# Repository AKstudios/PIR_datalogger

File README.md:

# PIR data logger
A motion/activity data logger that stores time-stamped data on a microSD card whenever there is motion within 3-5m. Approximate battery life: 1-2 years depending on LiPo battery used.

<p align="center">
  
  <br></br>
  
</p>

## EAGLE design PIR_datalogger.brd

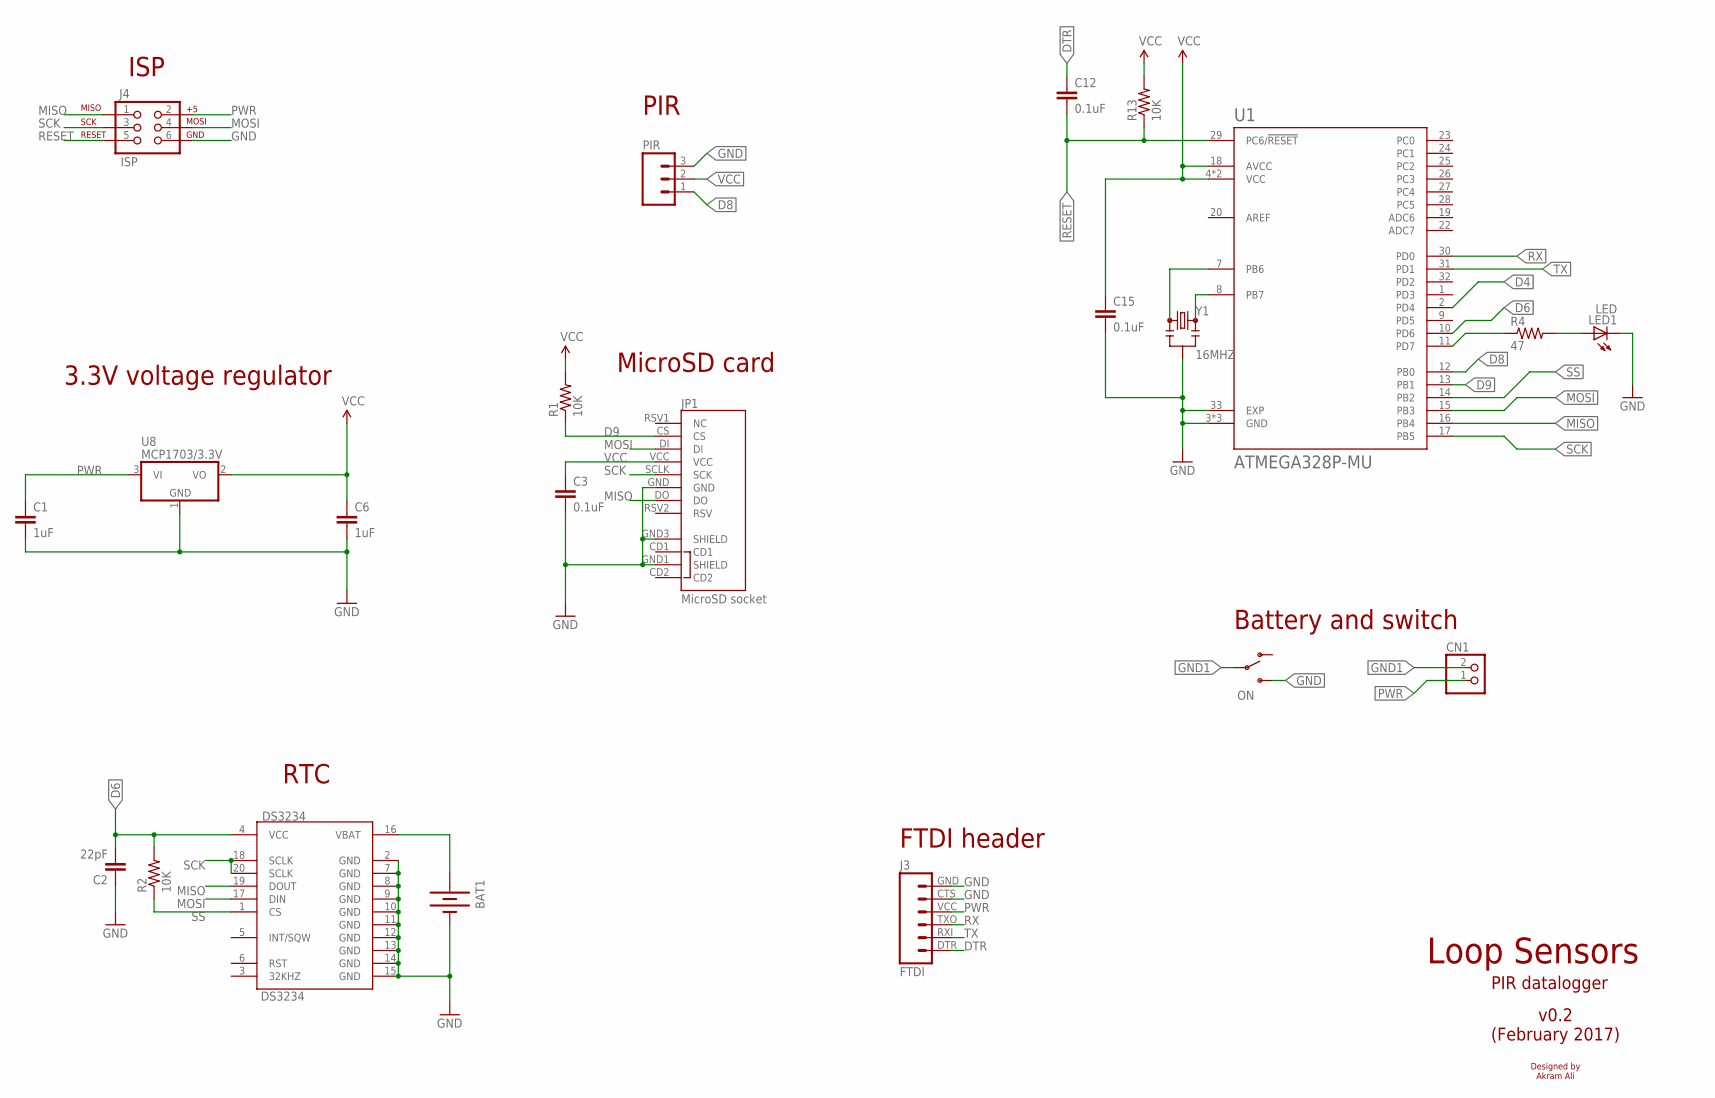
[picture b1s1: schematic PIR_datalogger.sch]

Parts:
BAT1: BATTERY12MM; BATTCON_12MM; MPN 3000
C1, C6: 1uF; 0805; MPN CC0805KKX7R7BB105
C2: 22pF; 0805; MPN AC0805KRX7R9BB104
C3, C12, C15: 0.1uF; 0805; MPN AC0805KRX7R9BB104
CN1: JST_2PIN-SMT-RA; JST-PH-2-SMT-RA
DS3234: DS3234; MPN DS3234S#
J3: FTDI; FTDI_BASIC
J4: ISP; 2X3
JP1: MicroSD socket; MICRO-SD-SOCKET-PP
LED1: LED; CHIPLED_0805; MPN 150080BS75000
ON: SWITCH-SPDT-SMD-A; SWITCH-SPST-SMD-A
PIR: M03PTH; 1X03
R1, R2, R13: 10K; 0805; MPN RC0805JR-0710KL
R4: 47; 0805; MPN RC0805JR-0747RL
U1: ATMEGA328P-MU; QFN50P500X500X100-33N
U8: MCP1703/3.3V; SOT23; MPN MCP1703T-2502E/CB
Y1: 16MHZ; RESONATOR-SMD; MPN CSTCE16M0V53-R0

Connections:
D4: U1.2 (PD4)
D6: C2.2, DS3234.4 (VCC), R2.2, U1.10 (PD6)
D8: PIR.1, U1.12 (PB0)
D9: JP1.CS, R1.1, U1.13 (PB1)
DTR: C12.1, J3.DTR (1)
GND: BAT1.GND (-), C1.2, C2.1, C3.2, C6.2, C15.2, DS3234.2 (GND), DS3234.7 (GND), DS3234.8 (GND), DS3234.9 (GND), DS3234.10 (GND), DS3234.11 (GND), DS3234.12 (GND), DS3234.13 (GND), DS3234.14 (GND), DS3234.15 (GND), J3.CTS (5), J3.GND (6), J4.6, JP1.GND, JP1.GND1 (SHIELD), JP1.GND3 (SHIELD), LED1.C, ON.3 (S), PIR.3, U1.3 (GND), U1.5 (GND), U1.21 (GND), U1.33 (EXP), U8.1 (GND), Y1.2
GND1: CN1.2 (1), ON.2
MISO: DS3234.19 (DOUT), J4.1, JP1.DO, U1.16 (PB4)
MOSI: DS3234.17 (DIN), J4.4, JP1.DI, U1.15 (PB3)
unnamed: R4.1, U1.11 (PD7)
unnamed: LED1.A, R4.2
unnamed: U1.8 (PB7), Y1.3
unnamed: U1.7 (PB6), Y1.1
unnamed: BAT1.PWR@1 (+), DS3234.16 (VBAT)
PWR: C1.1, CN1.1 (2), J3.VCC (4), J4.2, U8.3 (VI)
RESET: C12.2, J4.5, R13.1, U1.29 (PC6/!RESET)
RX: J3.TXO (3), U1.30 (PD0)
SCK: DS3234.18 (SCLK), DS3234.20 (SCLK), J4.3, JP1.SCLK (SCK), U1.17 (PB5)
SS: DS3234.1 (CS), R2.1, U1.14 (PB2)
TX: J3.RXI (2), U1.31 (PD1)
VCC: C3.1, C6.1, C15.1, JP1.VCC, PIR.2, R1.2, R13.2, U1.4 (VCC), U1.6 (VCC), U1.18 (AVCC), U8.2 (VO)

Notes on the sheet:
ISP
3.3V voltage regulator
Loop Sensors
PIR datalogger
v0.2 (February 2017)
Designed by Akram Ali
MicroSD card
RTC
PIR
FTDI header
Battery and switch

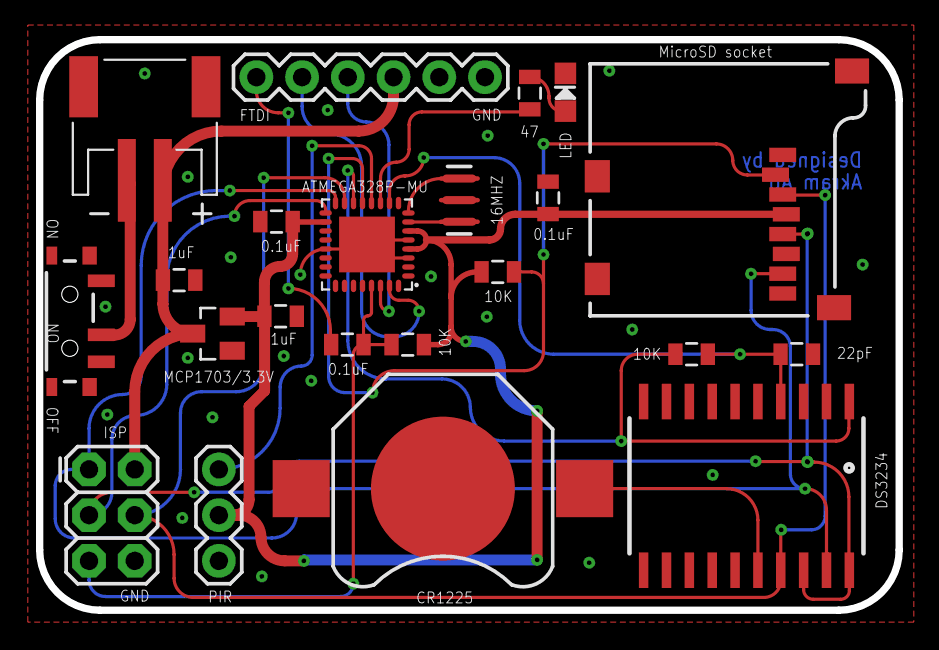
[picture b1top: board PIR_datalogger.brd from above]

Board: 2 copper layers, 47.8 x 31.7 mm, 22 parts (0 on the bottom side), 20 nets.

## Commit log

2017-01-27 :boom::camel: Added .gitattributes & .gitignore files
2017-01-27 Added EAGLE files
2017-01-28 Added OSH park renders
2017-02-15 v0.2 - design changes
    * Removed NPN transistor - microSD cards use their own sleep mode -
    keeping up with new SD protocol
    * Added decoupling cap to microSD card
    * Added pullups to microSD card and RTC
    * Adjusted some traces
2017-02-15 Updated OSH Park renders
    v0.2
2017-02-15 Deleted renders
2017-02-15 Added OSH Park renders
    v0.2
2017-02-15 v0.1 firmware added

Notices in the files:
parts and their libraries:
SparkFun-Passives: Licensing: Creative Commons ShareAlike 4.0 International - https://creativecommons.org/licenses/by-sa/4.0
